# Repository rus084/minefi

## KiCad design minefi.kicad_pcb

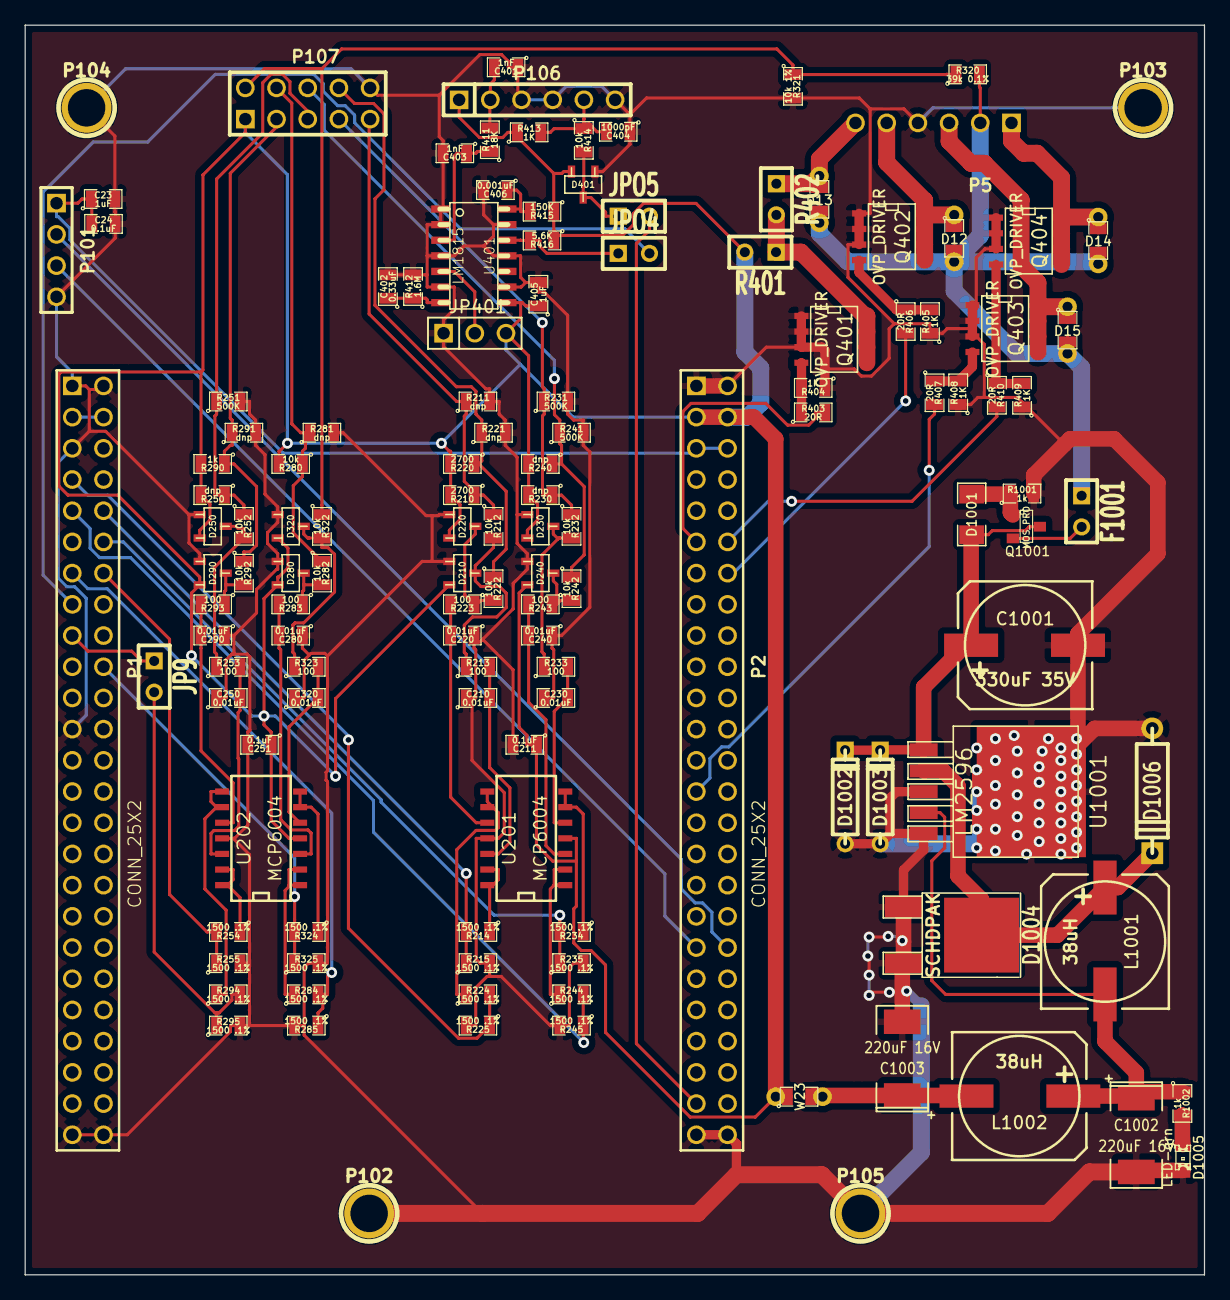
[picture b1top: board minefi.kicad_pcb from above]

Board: 2 copper layers, 96.0 x 101.7 mm, 133 parts (0 on the bottom side), 78 nets.

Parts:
C23, C405: 1uF; SM0805
C24, C211, C251: 0.1uF; SM0805
C210, C220, C230, C240, C250, C280, C290, C320: 0.01uF; SM0805
C401, C403: 1nF; SM0805
C402: 0.33uF; SM0805
C404: 1000pF; SM0805
C406: 0.001uF; SM0805
C1001: 330uF 35V; SMDSVP10
C1002, C1003: 220uF 16V; SM2512
D12, D13, D14, D15: DIODESCH; SM0805_jumper
D210, D220, D230, D240, D250, D280, D290, D320, D401: DOUBLE_SCHOTTKY; sot23
D1001: ZENERSMALL; SM1206
D1002, D1003: TVS; D3
D1004: SCHDPAK; DPAK2
D1005: LED-grn; LED-0805
D1006: DIODESCH; D4
F1001: 3.5A; SIL-2
JP9: TEST-AN; SIL-2
JP401: JP_3Way; PIN_ARRAY_3X1
JPO4: TEST-CRK; SIL-2
JPO5: TEST-CAM; SIL-2
L1001, L1002: 38uH; SMDSVP10
P1, P2: CONN_25X2; PIN_ARRAY_25x2_A
P5: CONN_3X2; pin_array_3x2
P101: CONN_4; PIN_ARRAY_4x1
P102, P103, P104, P105: CONN_1; 1pin
P106: CONN_6; PIN_ARRAY-6X1
P107: CONN_10; PIN_ARRAY_5x2_M
Q401, Q402, Q403, Q404: OVP_DRIVER; SO8E_ST
Q1001: MOS_PRO; SOT23
R210, R220: 2700; SM0805
R211, R221, R230, R240, R250, R281, R291: dnp; SM0805
R212, R222, R232, R242, R252, R280, R282, R292, R322, R414: 10k; SM0805
R213, R223, R233, R243, R253, R283, R293, R323: 100; SM0805
R214, R215, R224, R225, R234, R235, R244, R245, R254, R255, R284, R285, R294, R295, R324, R325: 1500 .1%; SM0805
R231, R241, R251: 500K; SM0805
R290, R1001, R1002: 1k; SM0805
R320: 39k 0.1%; SM0805
R321: 10k 1%; SM0805
R401: OPT; SIL-2
R402: 0R; SIL-2
R403, R406, R407, R410: 20R; SM0805
R404, R405, R408, R409, R413: 1K; SM0805
R411: 18K; SM0805
R412: 1.6M; SM0805
R415: 150K; SM0805
R416: 5.6K; SM0805
U201, U202: MCP6004; SO14N
U401: LM1815; AB2_SO14
U1001: LM2596; DPAK5
W23: TEST; SM0805_jumper

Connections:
/3.3V: C23.1, C24.1, P2.5, P2.6, P101.1
/PA5: JPO4.2, P1.15
/PC6: JPO5.2, P2.47
/PC10: P2.37, P101.3
/PC11: P2.38, P101.2
/PWR_buck_12V_switcher/5V-REG: C1003.1, L1002.2, W23.2
/PWR_buck_12V_switcher/FB: C1002.1, L1001.2, L1002.1, R1002.1, U1001.4
/PWR_buck_12V_switcher/OUT: D1004.2, D1006.2, L1001.1, U1001.2
/PWR_buck_12V_switcher/VBAT: C1001.1, D1001.2, D1002.2, D1003.2, Q1001.2, U1001.1
/PWR_buck_12V_switcher/Vf: F1001.2, Q1001.3
/VDD: P1.3, P1.4
/adc_amp_divider/5V: C211.1, C251.1, C405.1, D210.3, D220.3, D230.3, D240.3, D250.3, D280.3, D290.3, D320.3, D401.3, JP401.3, P2.3, P2.4, P106.1, P107.1, R210.2, R220.2, R230.2, R240.2, R250.2, R280.2, R290.2, R401.2, R413.1, R415.1, R416.1, U201.4, U202.4, U401.8, W23.1
/adc_amp_divider/12V_bat: D12.2, D13.2, D14.2, D15.2, F1001.1, P5.2, R320.2
/adc_amp_divider/INP1: P107.9, R210.1, R211.1, R212.1
/adc_amp_divider/INP2: P107.8, R220.1, R221.1, R222.1
/adc_amp_divider/INP3: P107.7, R230.1, R231.1, R232.1
/adc_amp_divider/INP4: P107.6, R240.1, R241.1, R242.1
/adc_amp_divider/INP5: P107.5, R250.1, R251.1, R252.1
/adc_amp_divider/INP8: P107.4, R280.1, R281.1, R282.1
/adc_amp_divider/INP9: P107.3, R290.1, R291.1, R292.1
/adc_amp_divider/INP12: P107.2, R320.1, R321.1, R322.1
/adc_amp_divider/OUT1: P1.10, R214.2, R215.1
/adc_amp_divider/OUT2: P1.7, R224.2, R225.1
/adc_amp_divider/OUT3: P1.12, R234.2, R235.1
/adc_amp_divider/OUT4: P1.9, R244.2, R245.1
/adc_amp_divider/OUT5: P1.14, R254.2, R255.1
/adc_amp_divider/OUT8: P1.13, R284.2, R285.1
/adc_amp_divider/OUT9: JP9.1, P1.17
/adc_amp_divider/OUT12: P1.20, R324.2, R325.1
/cps_vrs_io_1/CAM: D401.2, JPO5.1, R414.2
/cps_vrs_io_1/CAM+: C404.2, P106.5, R413.2, R414.1
/cps_vrs_io_1/CRANK: JPO4.1, R416.2, U401.12
/cps_vrs_io_1/CRK2+: C401.2, P106.2, R411.2
/inj_12ch/INJ-01: Q401.2, R401.1, R402.2
/inj_12ch/INJ-01_2: D13.1, P5.6, R402.1
/inj_12ch/INJ-01_5V: P2.11, R403.2
/inj_12ch/INJ-02: D12.1, P5.5, Q402.2
/inj_12ch/INJ-02_5V: P2.14, R406.2
/inj_12ch/INJ-03: D15.1, P5.3, Q403.2
/inj_12ch/INJ-03_5V: P2.27, R407.2
/inj_12ch/INJ-04: D14.1, P5.1, Q404.2
/inj_12ch/INJ-04_5V: P2.12, R410.2
GND: C23.2, C24.2, C210.1, C211.2, C220.1, C230.1, C240.1, C250.1, C251.2, C280.1, C290.1, C320.1, C401.1, C402.2, C403.2, C404.1, C405.2, C406.2, C1001.2, C1002.2, C1003.2, D210.1, D220.1, D230.1, D240.1, D250.1, D280.1, D290.1, D320.1, D401.1, D1002.1, D1003.1, D1004.1, D1004.3, D1005.2, D1006.1, JP401.1, P1.1, P1.2, P1.5, P1.23, P1.49, P1.50, P2.1, P2.2, P2.49, P2.50, P5.4, P101.4, P102.1, P103.1, P104.1, P105.1, P106.3, P106.4, P106.6, P107.10, Q401.3, Q402.3, Q403.3, Q404.3, R211.2, R215.2, R221.2, R225.2, R231.2, R235.2, R241.2, R245.2, R251.2, R255.2, R281.2, R285.2, R291.2, R295.2, R321.2, R325.2, R404.1, R405.1, R408.1, R409.1, R412.2, R1001.2, U201.11, U202.11, U401.1, U401.2, U401.4, U401.6, U401.9, U401.11, U401.13, U1001.3, U1001.5
unnamed: Q402.1, R405.2, R406.1
unnamed: Q404.1, R409.2, R410.1
unnamed: Q403.1, R407.1, R408.2
unnamed: Q401.1, R403.1, R404.2
unnamed: C250.2, R253.2, U202.12
unnamed: R254.1, U202.13, U202.14
unnamed: C280.2, R283.2, U202.3
unnamed: R244.1, U201.1, U201.2
unnamed: R234.1, U201.6, U201.7
unnamed: C230.2, R233.2, U201.5
unnamed: C240.2, R243.2, U201.3
unnamed: R284.1, U202.1, U202.2
unnamed: C320.2, R323.2, U202.5
unnamed: D320.2, R322.2, R323.1
unnamed: R324.1, U202.6, U202.7
unnamed: D210.2, R212.2, R213.1
unnamed: D220.2, R222.2, R223.1
unnamed: R294.1, U202.8, U202.9
unnamed: C290.2, R293.2, U202.10
unnamed: D250.2, R252.2, R253.1
unnamed: D290.2, R292.2, R293.1
unnamed: D280.2, R282.2, R283.1
unnamed: JP9.2, R294.2, R295.1
unnamed: D230.2, R232.2, R233.1
unnamed: D240.2, R242.2, R243.1
unnamed: C210.2, R213.2, U201.12
unnamed: R214.1, U201.13, U201.14
unnamed: C220.2, R223.2, U201.10
unnamed: R224.1, U201.8, U201.9
unnamed: C406.1, R415.2, U401.14
unnamed: C403.1, R411.1, U401.3
unnamed: JP401.2, U401.5
unnamed: C402.1, R412.1, U401.7
unnamed: D1001.1, Q1001.1, R1001.1
unnamed: D1005.1, R1002.2

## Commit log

2015-07-28 adding files
2015-07-28 progress
2015-07-29 vias and fill zones
2015-07-30 more width of power lines
2015-08-08 wider wires
2015-08-22 progress
    board is better
2015-09-01 vr input changed to lm1815
2015-09-01 forgot schematic and modules...
